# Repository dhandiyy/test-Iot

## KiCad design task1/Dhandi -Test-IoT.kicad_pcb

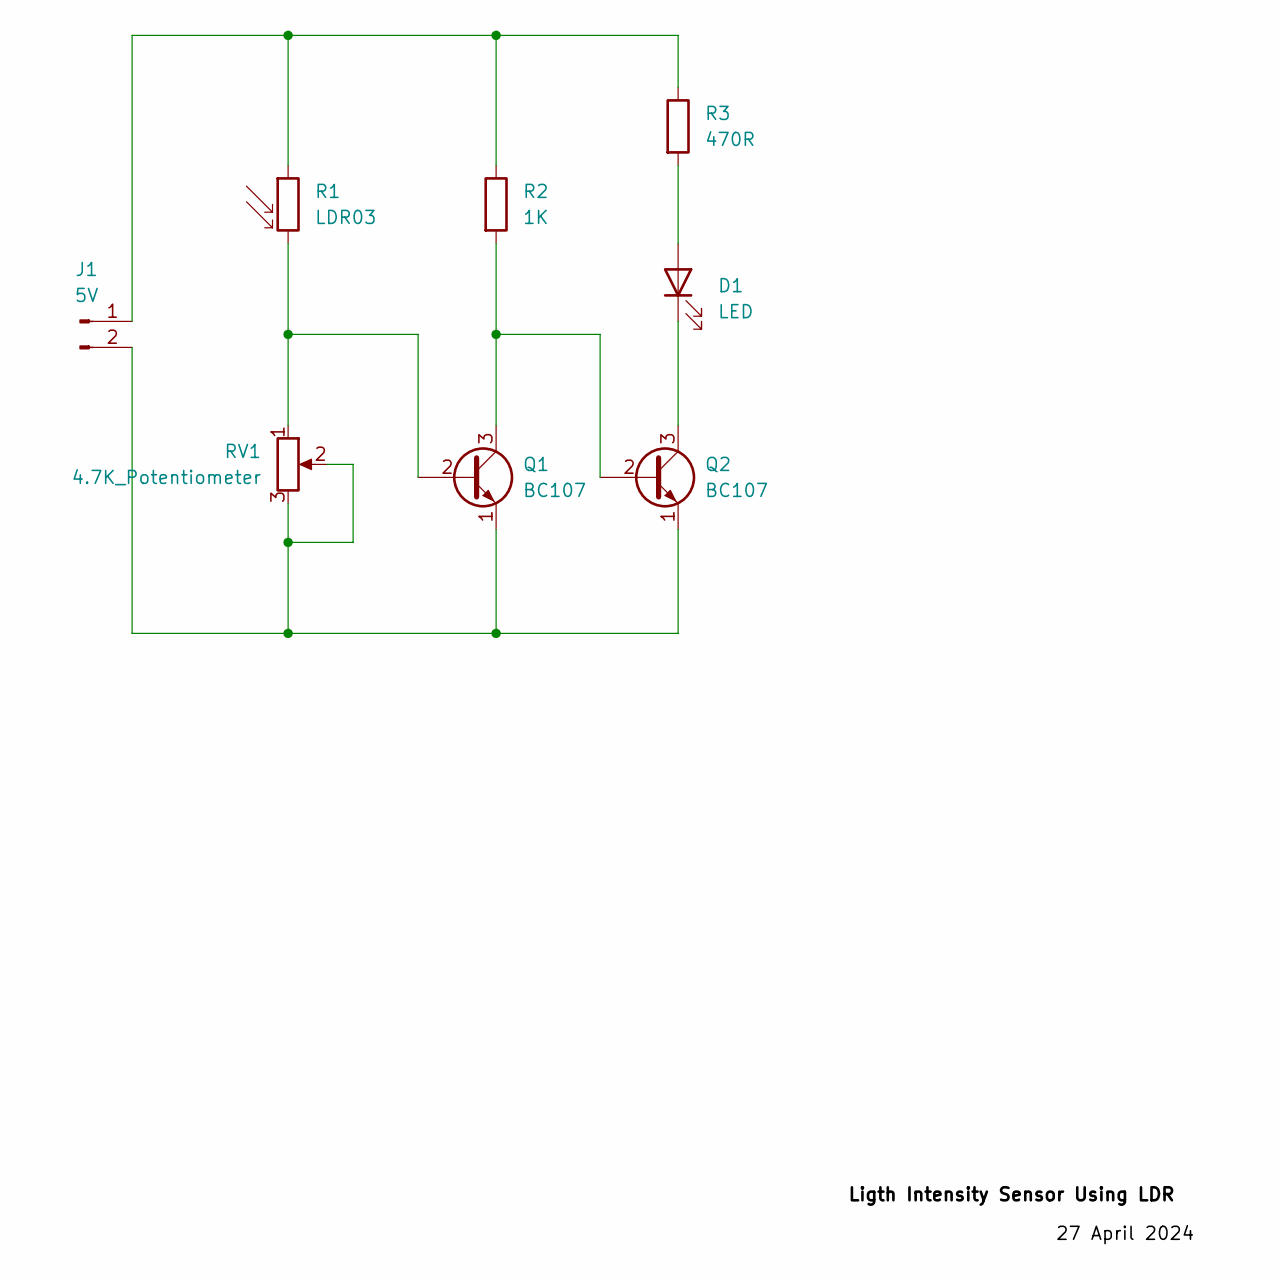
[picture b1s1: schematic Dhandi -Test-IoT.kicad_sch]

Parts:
D1: LED; LED_D5.0mm
J1: 5V; SolderWire-0.5sqmm_1x02_P4.8mm_D0.9mm_OD2.3mm
Q1, Q2: BC107; TO-18-3
R1: LDR03; R_LDR_10x8.5mm_P7.6mm_Vertical
R2: 1K; R_LDR_4.9x4.2mm_P2.54mm_Vertical
R3: 470R; R_LDR_4.9x4.2mm_P2.54mm_Vertical
RV1: 4.7K_Potentiometer; Potentiometer_Bourns_3006Y_Horizontal

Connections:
unnamed: D1.2 (A), R3.2
unnamed: D1.1 (K), Q2.3 (C)
unnamed: J1.1, R1.1, R2.1, R3.1
unnamed: J1.2, Q1.1 (E), Q2.1 (E), RV1.2, RV1.3
unnamed: Q1.2 (B), R1.2, RV1.1
unnamed: Q1.3 (C), Q2.2 (B), R2.2

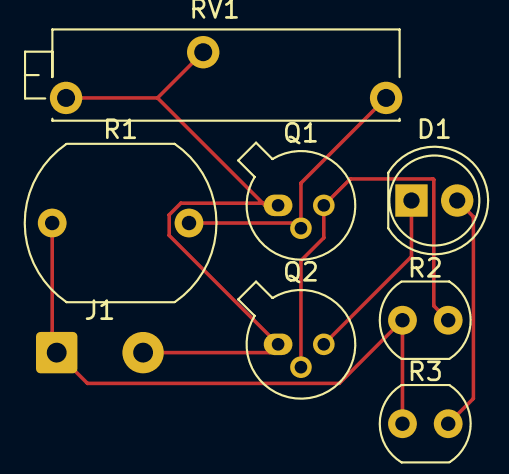
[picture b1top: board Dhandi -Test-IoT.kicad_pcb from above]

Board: 2 copper layers, 8 parts (0 on the bottom side), 6 nets.

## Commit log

2024-04-27 update file
